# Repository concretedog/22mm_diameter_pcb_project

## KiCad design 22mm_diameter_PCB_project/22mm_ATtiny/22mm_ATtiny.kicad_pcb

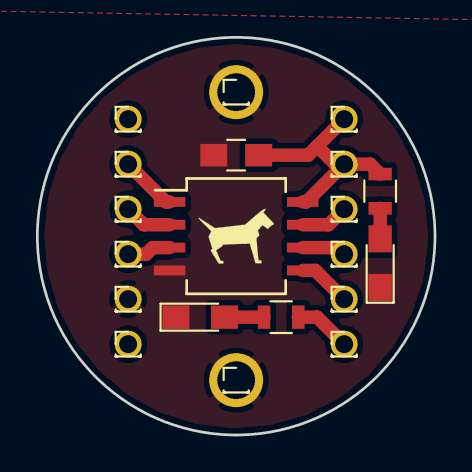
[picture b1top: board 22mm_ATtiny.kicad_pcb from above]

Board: 2 copper layers, 22.1 x 22.1 mm, 17 parts (0 on the bottom side), 10 nets.

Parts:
C1: C; C_0805_HandSoldering
D1, D2: LED; LED_0805_HandSoldering
J1, J2, J4, J5, J6, J8, J9, J12, J13, J15, J16: Conn_01x01; Pin_Header_Straight_1x01_Pitch1.00mm
R1, R2: R; R_0805
U1: ATTINY85-20SU; SO-8_5.3x6.2mm_Pitch1.27mm

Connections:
GND: C1.2, D1.1, D2.1, J12.1, J13.1, U1.4
unnamed: D1.2, R1.1
unnamed: D2.2, R2.2
unnamed: J1.1, U1.7
unnamed: J2.1, U1.2
unnamed: J4.1, U1.1
unnamed: J5.1, U1.5
unnamed: J6.1, U1.6
unnamed: J9.1, R1.2
VCC: C1.1, J8.1, R2.1, U1.8

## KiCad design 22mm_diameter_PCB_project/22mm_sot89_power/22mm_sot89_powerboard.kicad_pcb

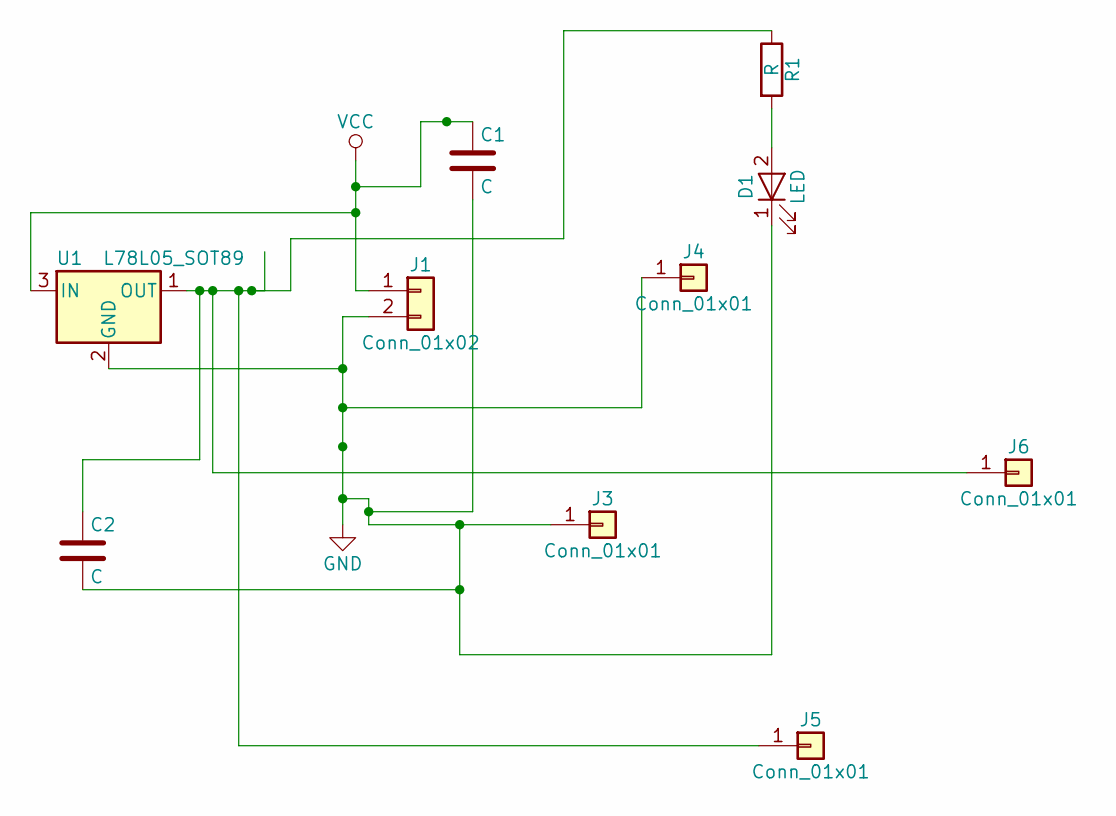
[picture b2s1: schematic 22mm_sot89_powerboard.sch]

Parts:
C1, C2: C; C_0805
D1: LED; LED_0805
J1: Conn_01x02; Pin_Header_Straight_1x02_Pitch2.54mm
J3, J4, J5, J6: Conn_01x01; Pin_Header_Straight_1x01_Pitch2.54mm
R1: R; R_0805
U1: L78L05_SOT89; SOT-89-3_Handsoldering

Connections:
GND: C1.2, C2.2, D1.1 (K), J1.2, J3.1, J4.1, U1.2 (GND)
unnamed: C2.1, J5.1, J6.1, R1.1, U1.1 (OUT)
unnamed: D1.2 (A), R1.2
VCC: C1.1, J1.1, U1.3 (IN)

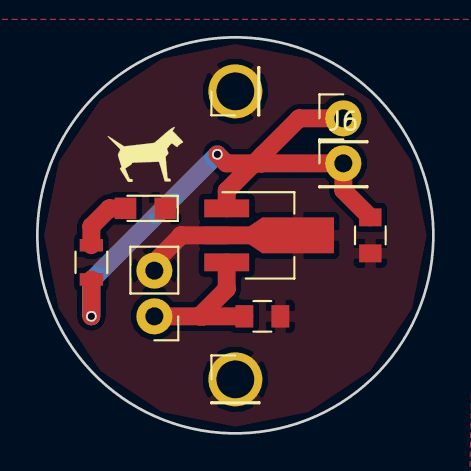
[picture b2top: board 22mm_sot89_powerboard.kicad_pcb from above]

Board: 2 copper layers, 22.0 x 22.0 mm, 10 parts (0 on the bottom side), 4 nets.
